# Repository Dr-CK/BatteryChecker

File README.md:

# BatteryChecker
 Checks alkaline batteries (AA, AAA & 9V)

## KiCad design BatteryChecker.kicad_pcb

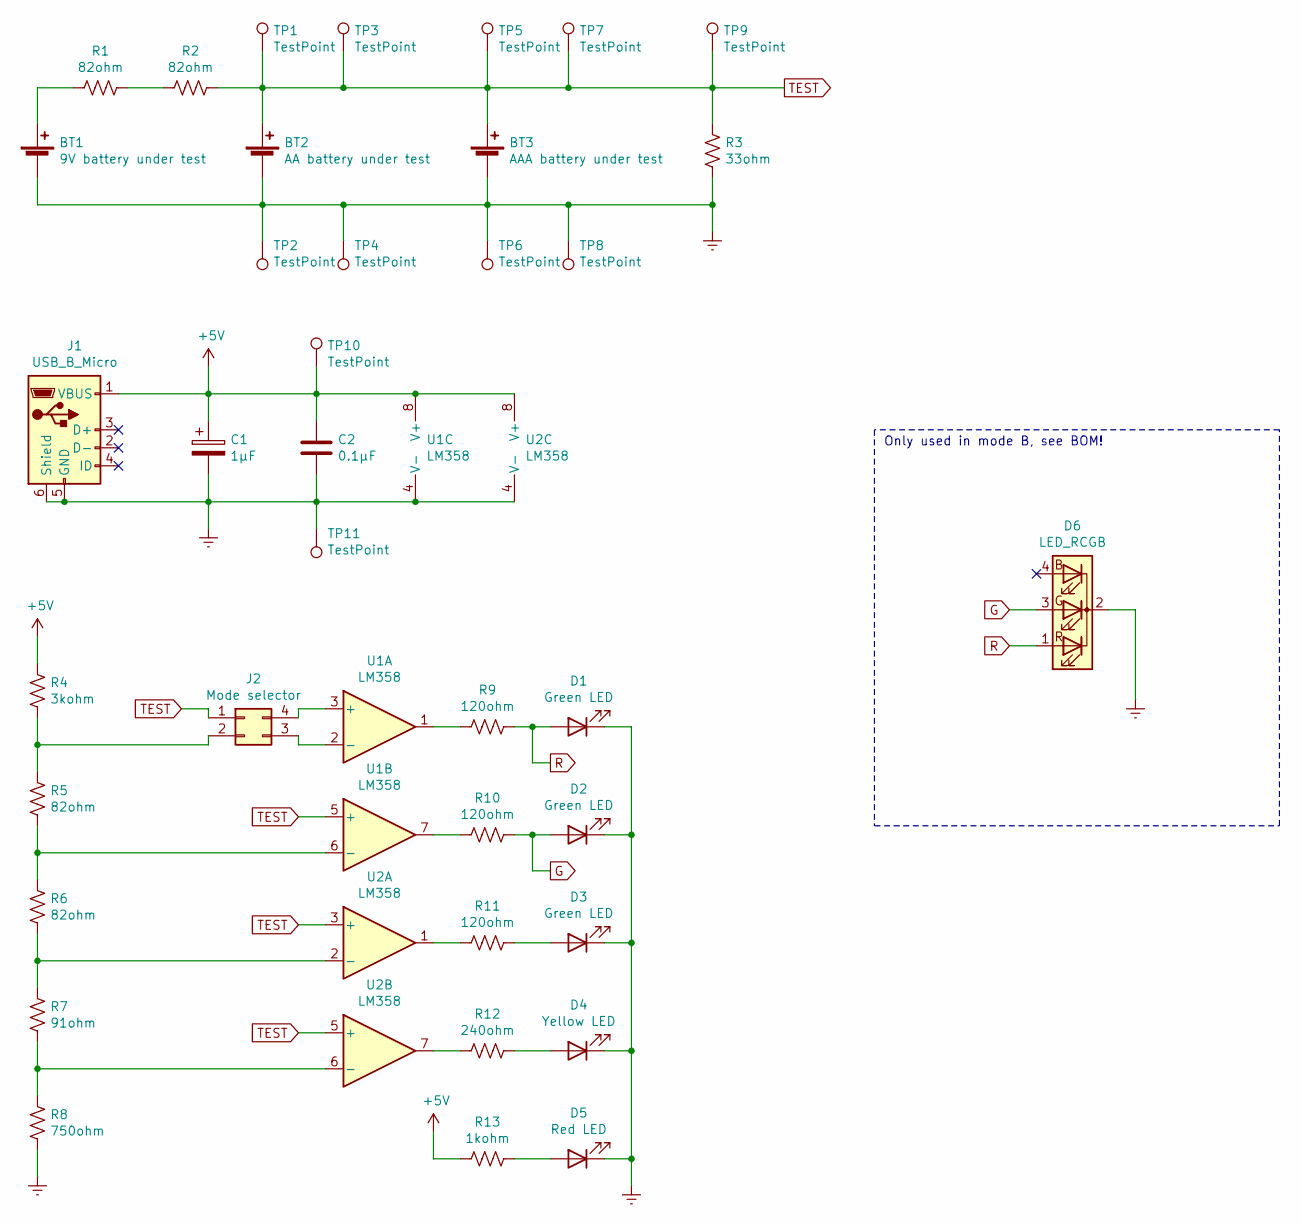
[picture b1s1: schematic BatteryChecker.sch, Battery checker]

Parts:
BT1: 9V battery under test; PinHeader_1x02_P2.54mm_Vertical
BT2: AA battery under test; BatteryHolder_Keystone_2460_1xAA
BT3: AAA battery under test; BatteryHolder_Keystone_2466_1xAAA
C1: 1µF; CP_Radial_D5.0mm_P2.50mm
C2: 0.1µF; C_Disc_D3.0mm_W1.6mm_P2.50mm
D1, D2, D3: Green LED; LED_D5.0mm
D4: Yellow LED; LED_D5.0mm
D5: Red LED; LED_D5.0mm
D6: LED_RCGB; LED_D5.0mm-4_RGB_Wide_Pins
J1: USB_B_Micro; USB_Micro-B_Amphenol_10118194_Horizontal
J2: Mode selector; PinHeader_2x02_P1.27mm_Vertical
R1, R2, R5, R6: 82ohm; R_Axial_DIN0207_L6.3mm_D2.5mm_P10.16mm_Horizontal
R3: 33ohm; R_Axial_DIN0207_L6.3mm_D2.5mm_P10.16mm_Horizontal
R4: 3kohm; R_Axial_DIN0207_L6.3mm_D2.5mm_P10.16mm_Horizontal
R7: 91ohm; R_Axial_DIN0207_L6.3mm_D2.5mm_P10.16mm_Horizontal
R8: 750ohm; R_Axial_DIN0207_L6.3mm_D2.5mm_P10.16mm_Horizontal
R9, R10, R11: 120ohm; R_Axial_DIN0207_L6.3mm_D2.5mm_P10.16mm_Horizontal
R12: 240ohm; R_Axial_DIN0207_L6.3mm_D2.5mm_P10.16mm_Horizontal
R13: 1kohm; R_Axial_DIN0207_L6.3mm_D2.5mm_P10.16mm_Horizontal
TP1, TP2, TP3, TP4, TP5, TP6, TP7, TP8: TestPoint; TestPoint_THTPad_D3.0mm_Drill1.5mm
TP9, TP10, TP11: TestPoint; TestPoint_Pad_D4.0mm
U1, U2: LM358; DIP-8_W7.62mm

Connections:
+5V: C1.1, C2.1, J1.1 (VBUS), R4.1, R13.2, TP10.1, U1.8 (V+), U2.8 (V+)
Earth: BT1.2 (-), BT2.2 (-), BT3.2 (-), C1.2, C2.2, D1.1 (K), D2.1 (K), D3.1 (K), D4.1 (K), D5.1 (K), D6.2 (K), J1.5 (GND), J1.6 (Shield), R3.2, R8.2, TP2.1, TP4.1, TP6.1, TP8.1, TP11.1, U1.4 (V-), U2.4 (V-)
G: D2.2 (A), D6.3 (GA), R10.1
unnamed: BT1.1 (+), R1.2
unnamed: D3.2 (A), R11.1
unnamed: D4.2 (A), R12.1
unnamed: D5.2 (A), R13.1
unnamed: J2.2, R4.2, R5.1
unnamed: J2.3, U1.2 (-)
unnamed: J2.4, U1.3 (+)
unnamed: R1.1, R2.2
unnamed: R5.2, R6.1, U1.6 (-)
unnamed: R6.2, R7.1, U2.2 (-)
unnamed: R7.2, R8.1, U2.6 (-)
unnamed: R9.2, U1.1
unnamed: R10.2, U1.7
unnamed: R11.2, U2.1
unnamed: R12.2, U2.7
R: D1.2 (A), D6.1 (RA), R9.1
TEST: BT2.1 (+), BT3.1 (+), J2.1, R2.1, R3.1, TP1.1, TP3.1, TP5.1, TP7.1, TP9.1, U1.5 (+), U2.3 (+), U2.5 (+)

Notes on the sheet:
Only used in mode B, see BOM!

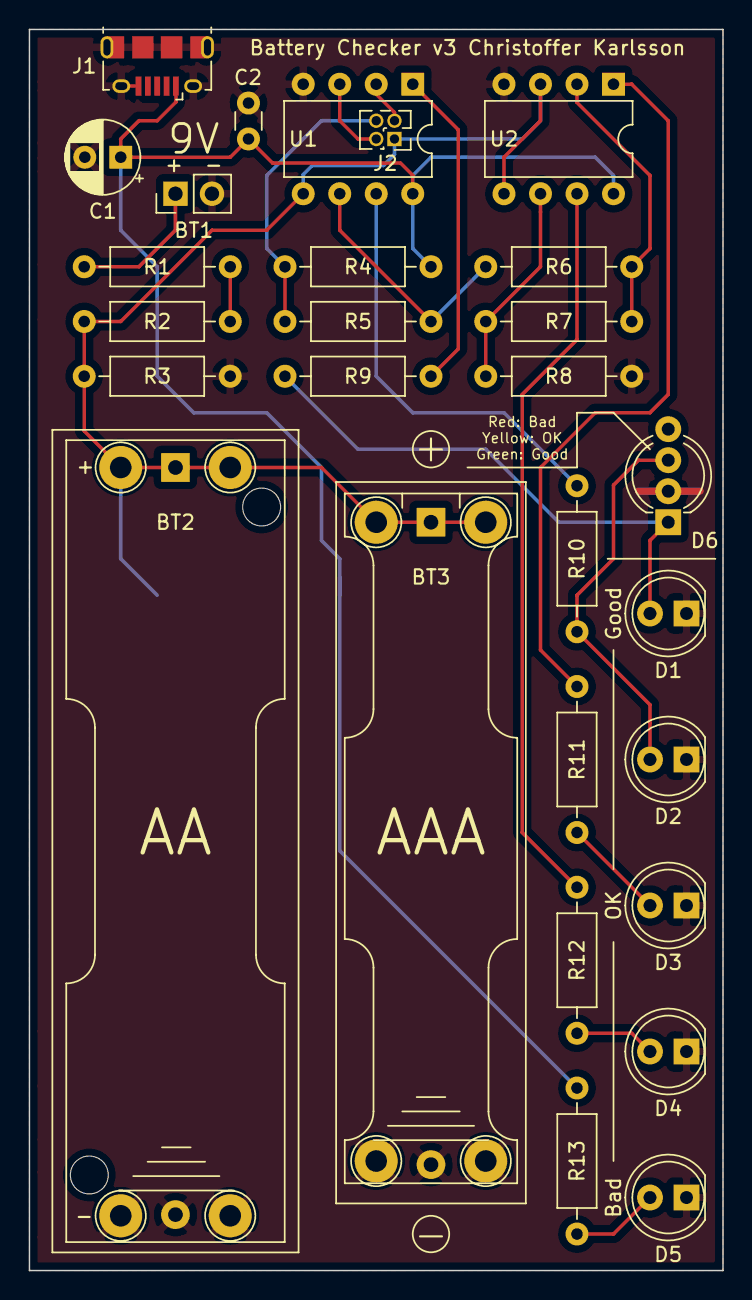
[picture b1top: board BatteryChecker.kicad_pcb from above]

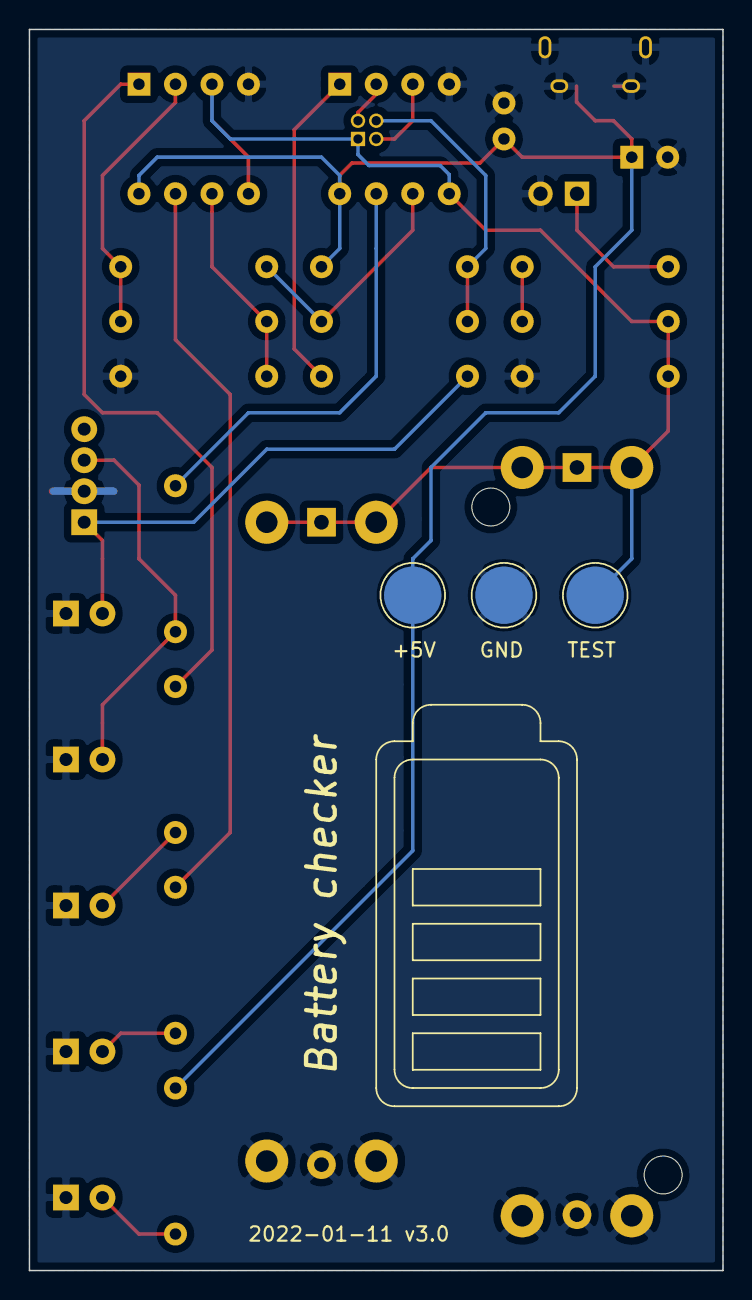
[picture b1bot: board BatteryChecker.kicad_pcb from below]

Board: 2 copper layers, 48.3 x 86.4 mm, 39 parts (3 on the bottom side), 20 nets.

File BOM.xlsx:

Battery checker
Code | Mode A | Mode B | Comment
 | 5 indicator LEDs | One RGB indicator LED
ICs
U1 | LM358 | LM358
U2 | LM358 | -
Resistors
R1 | 82 ohm, 0.25W | 82 ohm, 0.25W | *R1 & R2 only used for 9V batteries, can be substituted for one 160ohm 0.5W res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
R2 | 82 ohm, 0.25W | 82 ohm, 0.25W | *
R3 | 33 | 33 | For applying a load on the battery, as well as a voltage divider for the 9V bat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
R4 | 3k | 7.5k
R5 | 82 | 390
R6 | 82 | 1.8k
R7 | 91 | 0 (short)
R8 | 750 | 0 (short)
R9 | 120 | 10k
R10 | 120 | 120
R11 | 120 | -
R12 | 240 | -
R13 | 1k | -
Capacitors
C1 | (1µ) | (1µ) | Optional electrolytic capacitor; Square = anode
C2 | 0.1µ | 0.1µ
Diodes
D1 | Green LED | - | **Square = cathode
D2 | Green LED | - | **
D3 | Green LED | - | **
D4 | Yellow LED | - | **
D5 | Red LED | - | **
D6 | - | Common cathode RGB LED | RCG(B) pin order, square = red
Connectors
J1 | USB B micro connector | USB B micro connector | Only used to provide 5V for power and voltage reference
J2 | Short horizontally | Short vertically | Selects mode A or B
BT1 | 9V battery connector | 9V battery connector | ***Square = positive
BT2 | AA battery connector | AA battery connector | ***; ****For BT2 & BT3, use battery holder in center pins or simply some folded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
BT3 | AAA battery connector | AAA battery connector | ***; ****

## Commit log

2022-01-09 Schematic, PCB and BOM
2022-01-09 Updated v3.0
2022-01-11 Updated PCB and schematic
